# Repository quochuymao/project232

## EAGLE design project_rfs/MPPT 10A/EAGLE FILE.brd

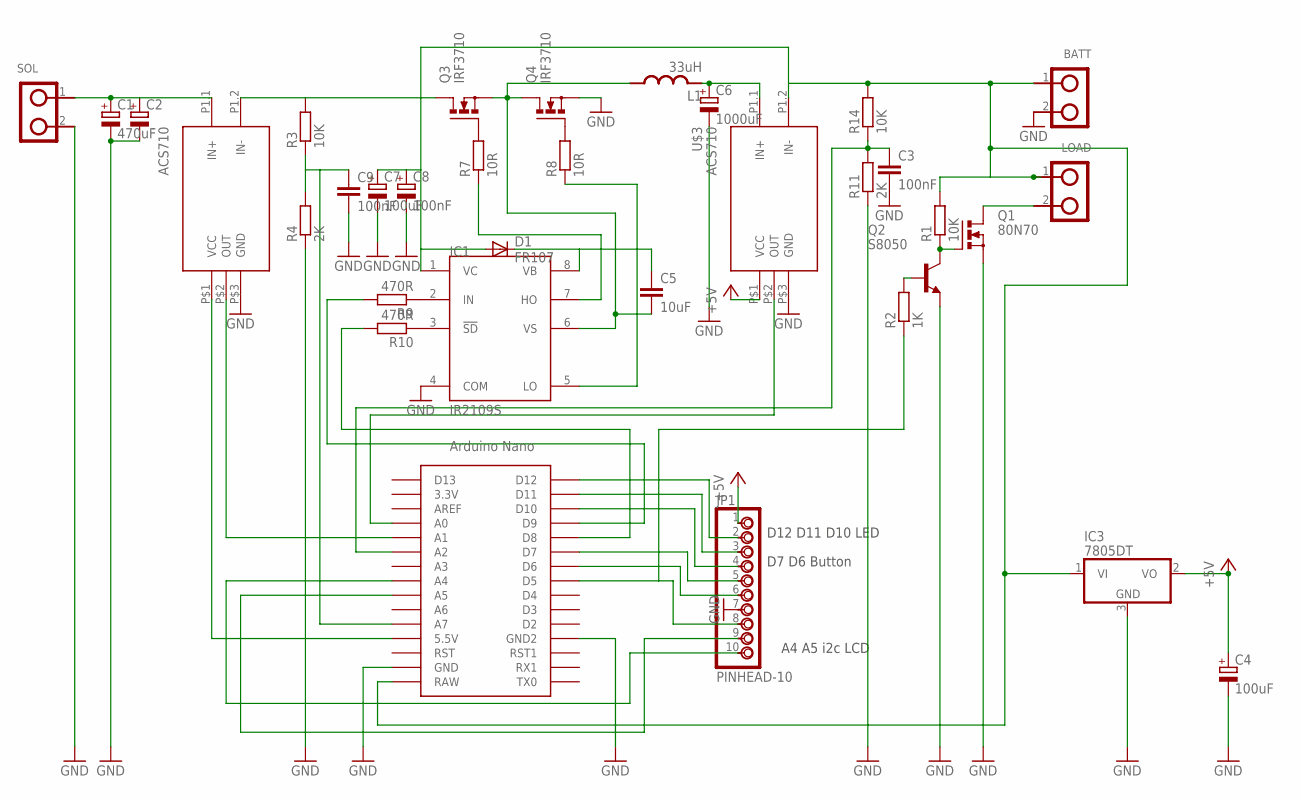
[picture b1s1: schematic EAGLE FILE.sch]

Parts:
.: ACS710; CURRENT-SENSOR-ACS712#IC
BATT: DOMINO-2; DOMI-2
C1: 470uF; E5-13
C2: CPOL-EUE5-13; E5-13
C3, C9: 100nF; C1206
C4, C7: 100uF; SMC_D
C5: 10uF; C1812
C6: 1000uF; E5-13
C8: 100nF; SMC_D
D1: FR107; SMB
IC1: IR2109S; SO08
IC3: 7805DT; TO252
JP1: PINHEAD-10
L1: 33uH; L-10
LOAD: DOMINO-2; DOMI-2
Q1: 80N70; TO220BV
Q2: S8050; TO92
Q3, Q4: IRF3710; TO220BV
R1, R3, R14: 10K; R1206
R2: 1K; R1206
R4, R11: 2K; R1206
R7, R8: 10R; R1206
R9, R10: 470R; R1206
SOL: DOMINO-2; DOMI-2
U$1: NANO
U$3: ACS710; CURRENT-SENSOR-ACS712#IC

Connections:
+5V: C4.+, IC3.2 (VO), JP1.1, U$3.P$1 (VCC)
GND: ..P$3 (GND), BATT.2, C1.-, C2.-, C3.2, C4.-, C6.-, C7.-, C8.-, C9.2, IC1.4 (COM), IC3.3 (GND), JP1.7, Q1.S, Q2.3 (E), Q4.S, R4.1, R11.1, SOL.2, U$1.GND, U$1.GND1 (GND2), U$3.P$3 (GND)
unnamed: ..P$1 (VCC), U$1.5V (5.5V)
unnamed: LOAD.2, Q1.D
unnamed: Q1.G, Q2.1 (C), R1.1
unnamed: Q2.2 (B), R2.2
unnamed: JP1.8, R2.1, U$1.D5
unnamed: ..P1.1 (IN+), C1.+, C2.+, SOL.1
unnamed: ..P1.2 (IN-), Q3.D, R3.2
unnamed: ..P$2 (OUT), U$1.A1
unnamed: C9.1, R3.1, R4.2, U$1.A7
unnamed: JP1.5, U$1.D7
unnamed: JP1.6, U$1.D6
unnamed: JP1.2, U$1.D12
unnamed: JP1.3, U$1.D11
unnamed: JP1.4, U$1.D10
unnamed: Q3.G, R7.2
unnamed: Q4.G, R8.2
unnamed: IC1.7 (HO), R7.1
unnamed: IC1.5 (LO), R8.1
unnamed: IC1.2 (IN), R9.1
unnamed: IC1.3 (!SD), R10.1
unnamed: R9.2, U$1.D9
unnamed: R10.2, U$1.D8
unnamed: U$1.A0, U$3.P$2 (OUT)
unnamed: C3.1, R11.2, R14.1, U$1.A2
unnamed: C6.+, L1.2, U$3.P1.1 (IN+)
unnamed: JP1.10, U$1.A4
unnamed: JP1.9, U$1.A5
VB: C5.1, D1.C, IC1.8 (VB)
VCCS: BATT.1, C7.+, C8.+, D1.A, IC1.1 (VC), IC3.1 (VI), LOAD.1, R1.2, R14.2, U$1.RAW, U$3.P1.2 (IN-)
VS: C5.2, IC1.6 (VS), L1.1, Q3.S, Q4.D

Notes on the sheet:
D12 D11 D10 LED
D7 D6 Button
A4 A5 i2c LCD

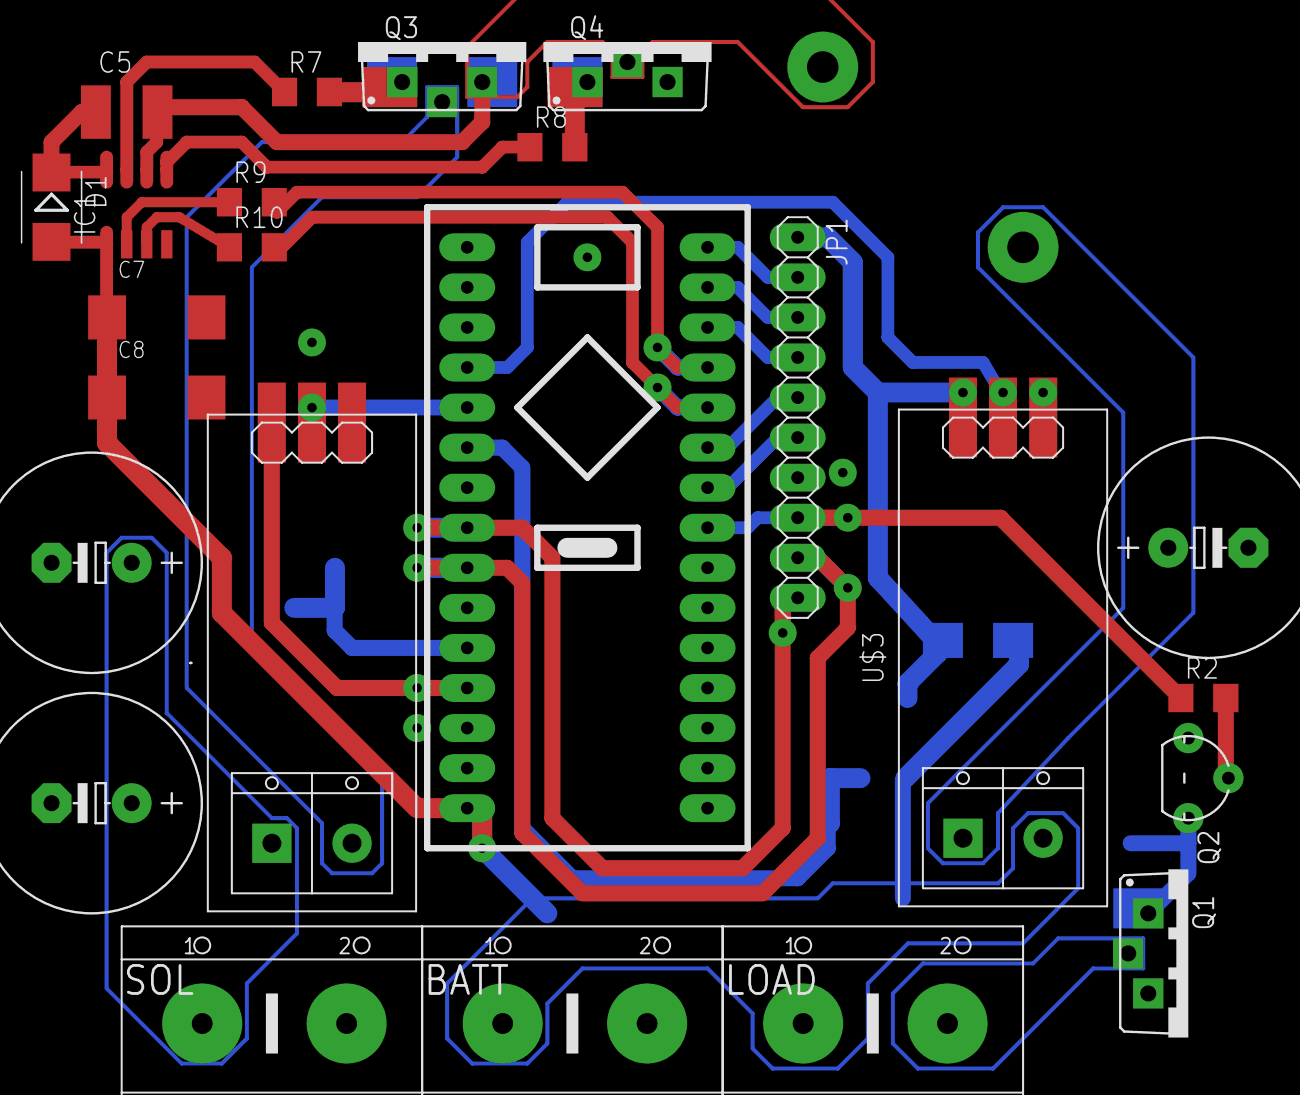
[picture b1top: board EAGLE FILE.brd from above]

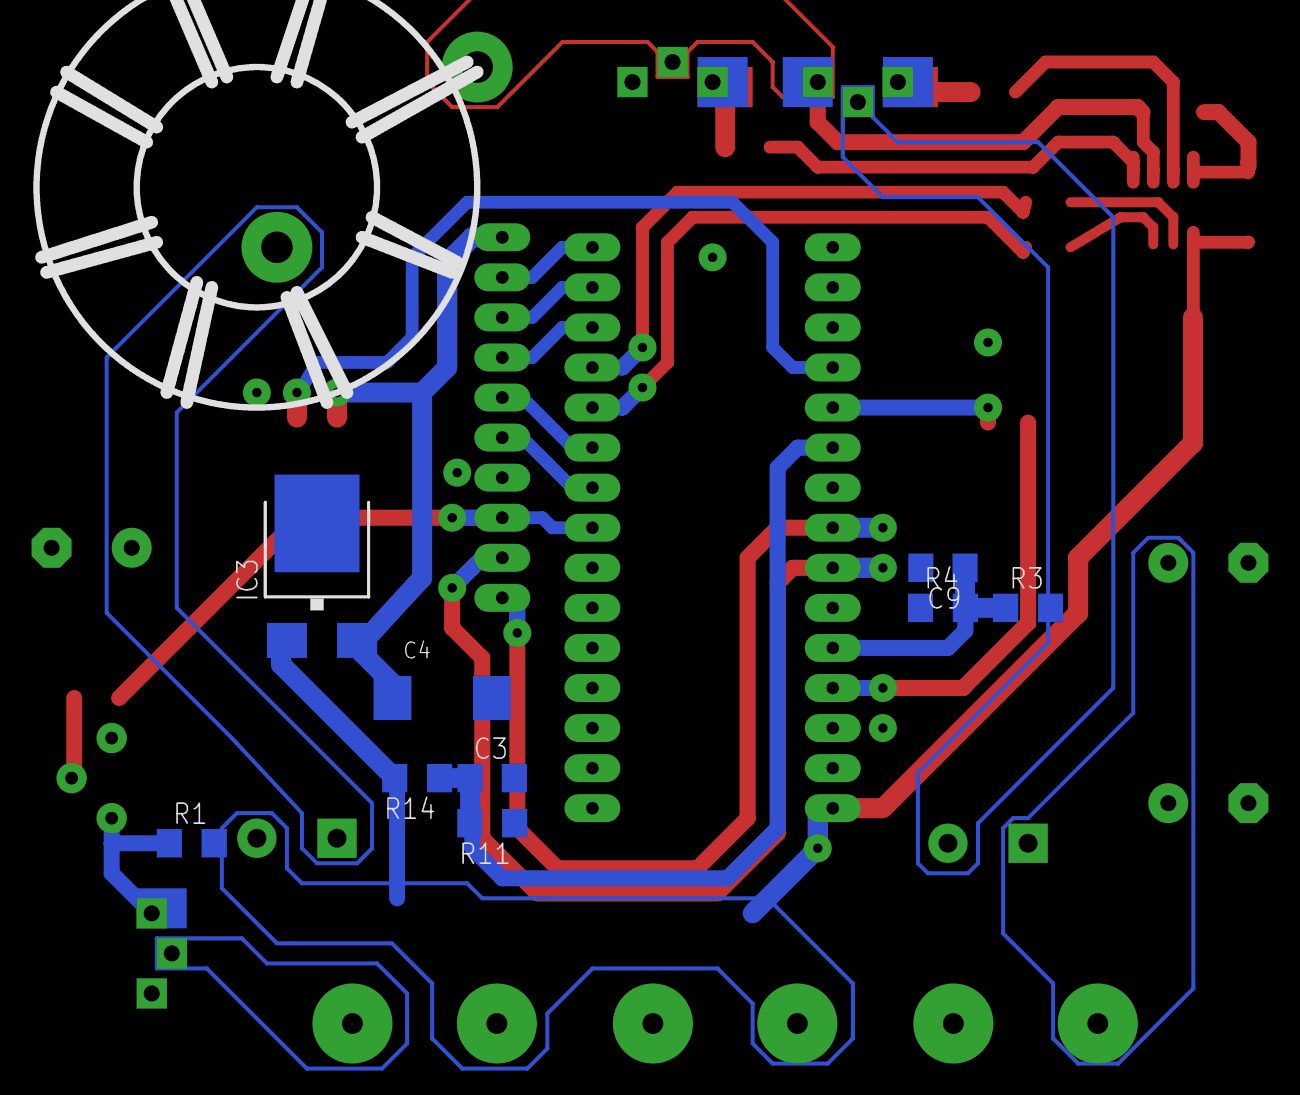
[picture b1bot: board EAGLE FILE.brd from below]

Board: 2 copper layers, 34 parts (10 on the bottom side), 32 nets.

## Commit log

2024-04-10 fist commit
2024-04-10 adding hardware file
2024-04-10 update firmware
2024-04-10 adding datasheet file
2024-04-19 update test board and docs
2024-04-22 update PIN in firmware
2024-04-25 add firmware_API_docs
2024-05-08 Update PCB
2024-05-08 update LCD and ADC function
2024-05-08 update GPIO, PWM function
2024-05-08 add API docs for STM32F103C8T6
2024-05-11 add LCD
2024-05-11 update gerber files
2024-05-11 fix PWM fucntion
2024-05-11 update PWM fucntion
2024-05-11 add docs function
2024-05-12 update code for main - project
2024-05-12 update firmware docs
2024-05-14 conflict fix
2024-05-15 update PCB Board V2
2024-05-16 commmit to push
2024-05-16 test PWM
2024-05-16 test lcd
2024-05-16 update LCD function
2024-05-16 push to pull
2024-05-16 update main
2024-05-23 update flowchart for firmware
2024-05-30 update 30/05/2024
2024-05-30 update code
2024-05-30 update 31/05
2024-06-02 update firmware files

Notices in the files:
parts and their libraries:
diy-modules: Released under the Creative Commons Attribution 4.0 International License: http://creativecommons.org/licenses/by/4.0
